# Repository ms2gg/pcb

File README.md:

# MS2GG Printed Circuit Board

Files for the production of the PCB for the *MS2GG* Master System to Game Gear
converter, for use with Kicad version 5.1 or later.

Please check out [the Wiki](https://github.com/ms2gg/doc/wiki) for details.

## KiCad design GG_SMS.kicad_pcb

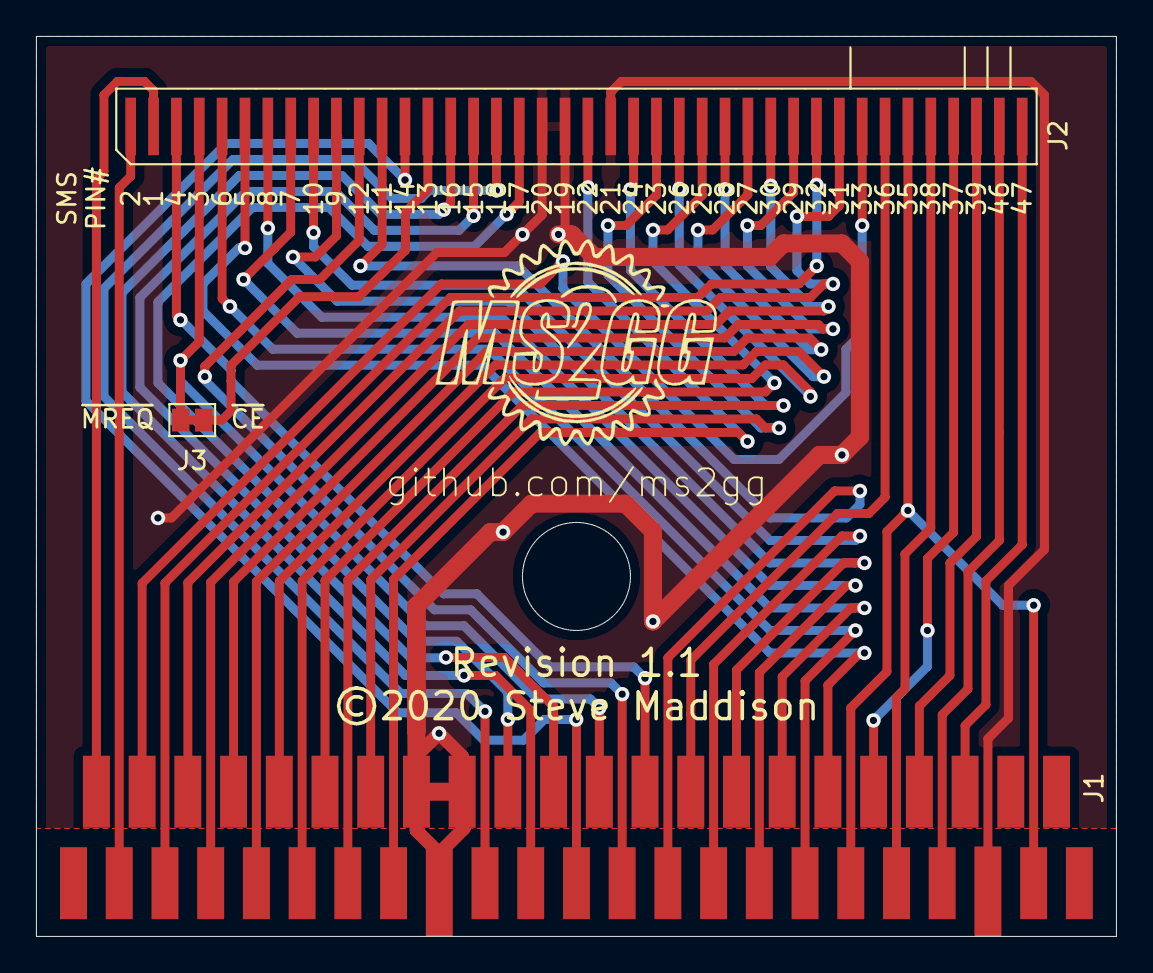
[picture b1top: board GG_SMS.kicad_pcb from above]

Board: 2 copper layers, 60.0 x 50.0 mm, 3 parts (0 on the bottom side), 36 nets.

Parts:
J1: GG Edge M; GG_EDGE
J2: Extension SMS; SMD_Ribbon_40
J3: ~CE~/~MREQ~; GS2

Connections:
+5V: J1.2, J1.35, J1.43, J2.2, J2.35
A0: J1.12, J2.26
A1: J1.11, J2.25
A2: J1.10, J2.28
A3: J1.9, J2.27
A4: J1.8, J2.30
A5: J1.7, J2.29
A6: J1.6, J2.32
A7: J1.5, J2.31
A8: J1.31, J2.7
A9: J1.30, J2.10
A10: J1.25, J2.11
A11: J1.29, J2.9
A12: J1.4, J2.33
A13: J1.32, J2.8
A14: J1.33, J2.5
A15: J1.28, J2.34
CLOCK: J1.40, J2.40
D0: J1.13, J2.23
D1: J1.14, J2.24
D2: J1.15, J2.21
D3: J1.19, J2.17
D4: J1.20, J2.18
D5: J1.21, J2.15
D6: J1.22, J2.16
D7: J1.23, J2.13
GND: J1.16, J1.17, J1.18, J1.41, J2.19, J2.20, J2.22
~CE: J1.24, J2.4, J2.14, J3.1, J3.2
~EXM1: J1.34, J2.6
~EXM2: J1.27, J2.12
~IOREQ: J1.37, J2.36
~M1: J1.36, J2.37
~RD: J1.26, J2.3
~RESET: J1.39, J2.39
~RFSH: J1.38, J2.38
~WR: J1.3, J2.1

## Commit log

2020-07-01 Initial commit.
2020-07-03 Add Wiki link.
2020-07-11 Ignore Gerbers in plots.

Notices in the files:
GG_SMS.kicad_pcb:
©2020 Steve Maddison
